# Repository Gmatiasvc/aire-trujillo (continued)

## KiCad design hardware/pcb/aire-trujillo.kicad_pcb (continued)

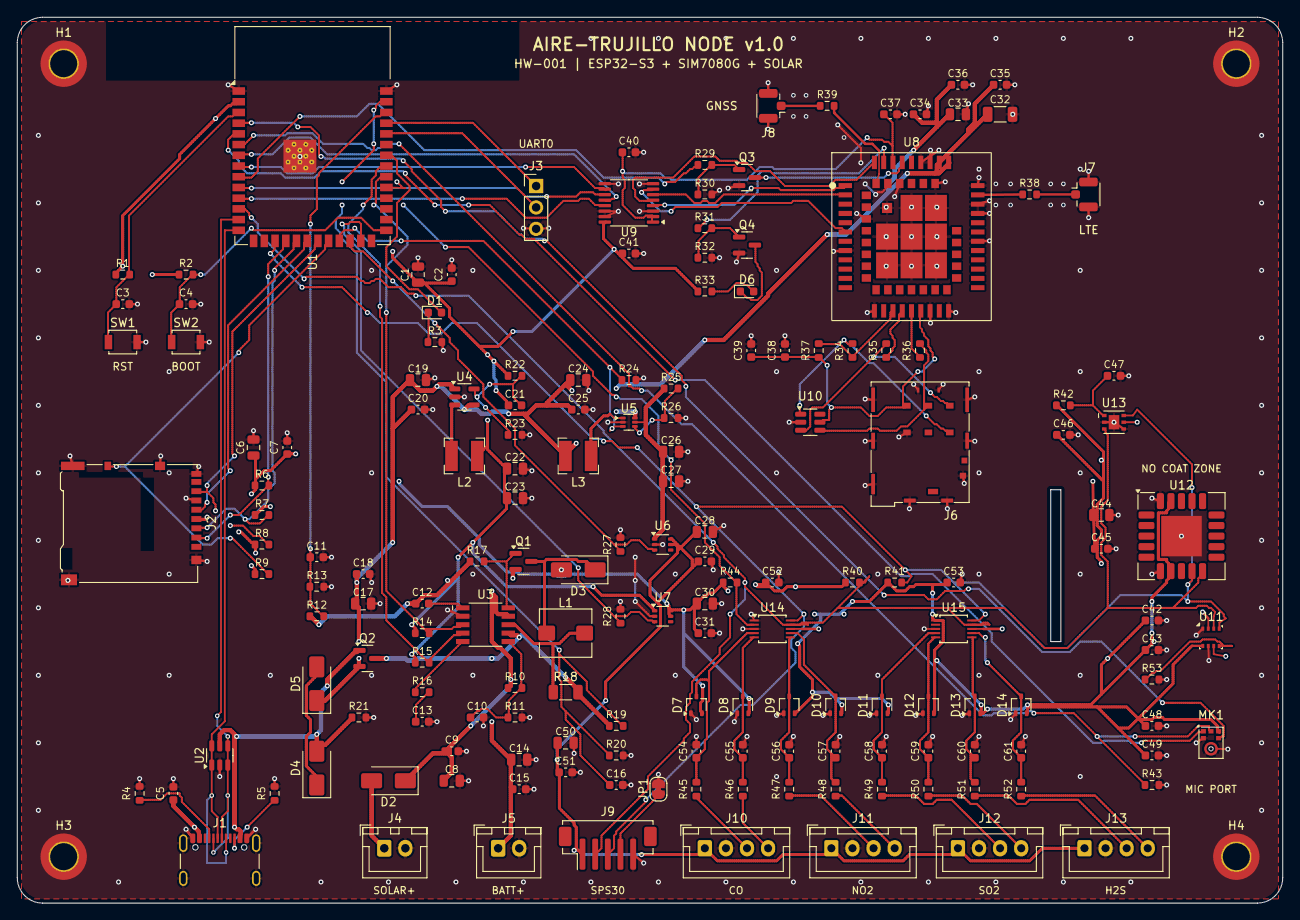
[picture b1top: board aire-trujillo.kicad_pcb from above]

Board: 4 copper layers, 150.0 x 105.0 mm, 171 parts (0 on the bottom side), 96 nets.

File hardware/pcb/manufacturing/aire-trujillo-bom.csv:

"Refs","Value","Footprint","Qty","DNP"
"C1,C6,C8,C19,C24,C28,C30,C33,C44,C50","10uF","Capacitor_SMD:C_0805_2012Metric","10",""
"C2,C4,C5,C7,C9,C11,C12,C15,C16,C18,C20,C25,C29,C31,C35,C38,C40-C43,C45,C47,C48,C51-C61","100nF","Capacitor_SMD:C_0603_1608Metric","34",""
"C3,C34,C37,C46,C49","1uF","Capacitor_SMD:C_0603_1608Metric","5",""
"C10","10nF","Capacitor_SMD:C_0603_1608Metric","1",""
"C13","220nF","Capacitor_SMD:C_0603_1608Metric","1",""
"C14,C17,C22,C23,C26,C27","22uF","Capacitor_SMD:C_0805_2012Metric","6",""
"C21","10pF","Capacitor_SMD:C_0603_1608Metric","1",""
"C32","100uF","Capacitor_SMD:C_1206_3216Metric","1",""
"C36,C39","33pF","Capacitor_SMD:C_0603_1608Metric","2",""
"D1","GREEN","LED_SMD:LED_0603_1608Metric","1",""
"D2-D5","SS34","Diode_SMD:D_SMA","4",""
"D6","BLUE_NET","LED_SMD:LED_0603_1608Metric","1",""
"D7-D14","BAT54S","Package_TO_SOT_SMD:SOT-323_SC-70","8",""
"H1-H4","M3_IP66","MountingHole:MountingHole_3.2mm_M3_ISO14580_Pad_TopBottom","4",""
"J1","USB4105-xx-A","Connector_USB:USB_C_Receptacle_GCT_USB4105-xx-A_16P_TopMnt_Horizontal","1",""
"J2","DM3AT-SF-PEJM5","Connector_Card:microSD_HC_Hirose_DM3AT-SF-PEJM5","1",""
"J3","UART0_DBG","Connector_PinHeader_2.54mm:PinHeader_1x03_P2.54mm_Vertical","1",""
"J4","SOLAR_IN","Connector_JST:JST_XH_B2B-XH-A_1x02_P2.50mm_Vertical","1",""
"J5","BATT_1S_LIION","Connector_JST:JST_XH_B2B-XH-A_1x02_P2.50mm_Vertical","1",""
"J6","SF72S006_1V8_SIM","Connector_JAE:JAE_SIM_Card_SF72S006","1",""
"J7","LTE_ANT_UFL","Connector_Coaxial:U.FL_Hirose_U.FL-R-SMT-1_Vertical","1",""
"J8","GNSS_ANT_UFL","Connector_Coaxial:U.FL_Hirose_U.FL-R-SMT-1_Vertical","1",""
"J9","SPS30_ZHR5","Connector_JST:JST_ZH_B5B-ZR-SM4-TF_1x05-1MP_P1.50mm_Vertical","1",""
"J10","ZE03_CO_XH4","Connector_JST:JST_XH_B4B-XH-A_1x04_P2.50mm_Vertical","1",""
"J11","ZE03_NO2_XH4","Connector_JST:JST_XH_B4B-XH-A_1x04_P2.50mm_Vertical","1",""
"J12","ZE03_SO2_XH4","Connector_JST:JST_XH_B4B-XH-A_1x04_P2.50mm_Vertical","1",""
"J13","ZE03_H2S_XH4","Connector_JST:JST_XH_B4B-XH-A_1x04_P2.50mm_Vertical","1",""
"JP1","I2C_SEL","Jumper:SolderJumper-2_P1.3mm_Bridged_RoundedPad1.0x1.5mm","1",""
"L1","22uH","Inductor_SMD:L_Bourns_SRP5030T","1",""
"L2","1.5uH","Inductor_SMD:L_Bourns-SRN4018","1",""
"L3","1.0uH","Inductor_SMD:L_Bourns-SRN4018","1",""
"MK1","ICS-43434","Sensor_Audio:InvenSense_ICS-43434-6_3.5x2.65mm","1",""
"Q1,Q2","AO3401A","Package_TO_SOT_SMD:SOT-23","2",""
"Q3,Q4","BSS138","Package_TO_SOT_SMD:SOT-23","2",""
"R1,R2,R6-R9,R14,R15,R17,R37,R44","10k","Resistor_SMD:R_0603_1608Metric","11",""
"R3,R29,R31,R33,R45-R52","1k","Resistor_SMD:R_0603_1608Metric","12",""
"R4,R5","5.1k","Resistor_SMD:R_0603_1608Metric","2",""
"R10,R19-R21,R23,R24,R26-R28,R30,R32,R43","100k","Resistor_SMD:R_0603_1608Metric","12",""
"R11","16.5k","Resistor_SMD:R_0603_1608Metric","1",""
"R12","470k","Resistor_SMD:R_0603_1608Metric","1",""
"R13","47k","Resistor_SMD:R_0603_1608Metric","1",""
"R16","120R","Resistor_SMD:R_0603_1608Metric","1",""
"R18","0.12R_1W","Resistor_SMD:R_1206_3216Metric","1",""
"R22","453k","Resistor_SMD:R_0603_1608Metric","1",""
"R25","732k","Resistor_SMD:R_0603_1608Metric","1",""
"R34-R36","22","Resistor_SMD:R_0603_1608Metric","3",""
"R38,R39","0R_RF","Resistor_SMD:R_0603_1608Metric","2",""
"R40,R41","4.7k","Resistor_SMD:R_0603_1608Metric","2",""
"R42","22R","Resistor_SMD:R_0603_1608Metric","1",""
"R53","0R","Resistor_SMD:R_0603_1608Metric","1",""
"SW1","RST","Button_Switch_SMD:SW_SPST_B3U-1000P","1",""
"SW2","BOOT","Button_Switch_SMD:SW_SPST_B3U-1000P","1",""
"U1","ESP32-S3-WROOM-1-N16R8","RF_Module:ESP32-S3-WROOM-1","1",""
"U2","USBLC6-2SC6","Package_TO_SOT_SMD:SOT-23-6","1",""
"U3","CN3791","aire-trujillo:cn3791","1",""
"U4","TLV62569DBV","Package_TO_SOT_SMD:SOT-23-5","1",""
"U5","TPS61023DRLR","Package_TO_SOT_SMD:SOT-563","1",""
"U6,U7","TPS22919DCKR","Package_TO_SOT_SMD:SOT-363_SC-70-6","2",""
"U8","SIM7080G","aire-trujillo:SIMCom_SIM7080G","1",""
"U9","SN74AVC4T245PW","Package_SO:TSSOP-16_4.4x5mm_P0.65mm","1",""
"U10","ESDA6V1-5SC6","Package_TO_SOT_SMD:SOT-23-6","1",""
"U11","BME280","Package_LGA:Bosch_LGA-8_2.5x2.5mm_P0.65mm_ClockwisePinNumbering","1",""
"U12","SCD41-D-R2","Sensor:Sensirion_SCD4x-1EP_10.1x10.1mm_P1.25mm_EP4.8x4.8mm","1",""
"U13","SGP40","aire-trujillo:sgp40","1",""
"U14","ADS1115_CO_NO2","Package_SO:TSSOP-10_3x3mm_P0.5mm","1",""
"U15","ADS1115_SO2_H2S","Package_SO:TSSOP-10_3x3mm_P0.5mm","1",""

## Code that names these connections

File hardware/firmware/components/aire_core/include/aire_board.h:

#ifndef AIRE_BOARD_H
#define AIRE_BOARD_H

/*
 * aire-trujillo — Mapa Definitivo de Pines, Buses y Reglas de Hardware (HW-001 v1.0)
 * MCU: ESP32-S3-WROOM-1-N16R8 (16 MB QIO Flash / 8 MB Octal PSRAM)
 * Sincronizado exactamente con hardware/doc/specs.md y aire-trujillo.kicad_pcb.
 */

/* Bus I2S — InvenSense ICS-43434 (MK1, Canal Izquierdo LR=GND) */
#define AIRE_GPIO_I2S_SCK       4
#define AIRE_GPIO_I2S_WS        5
#define AIRE_GPIO_I2S_SD        6

/* Módem Celular / GNSS — SIMCom SIM7080G (U8) vía SN74AVC4T245 (U9) y BSS138 (Q3) */
#define AIRE_GPIO_MODEM_STATUS  7
#define AIRE_GPIO_MODEM_DTR     15
#define AIRE_GPIO_MODEM_PWRKEY  16
#define AIRE_GPIO_MODEM_TXD     17   /* ESP32 TX -> U8 RXD */
#define AIRE_GPIO_MODEM_RXD     18   /* ESP32 RX <- U8 TXD */

/* Bus I2C Principal (3.3 V conmutado 3V3_SENS, R40/R41 4.7k pull-ups) */
#define AIRE_GPIO_I2C_SDA       8
#define AIRE_GPIO_I2C_SCL       9
#define AIRE_I2C_FREQ_HZ        100000U

/* Direcciones I2C de 7 bits verificadas en esquemático */
#define AIRE_I2C_ADDR_ADS1115_1 0x48U  /* U14: ADDR=GND -> CO (AIN0/1), NO2 (AIN2/3) */
#define AIRE_I2C_ADDR_ADS1115_2 0x49U  /* U15: ADDR=3V3_SENS -> SO2 (AIN0/1), H2S (AIN2/3) */
#define AIRE_I2C_ADDR_SGP40     0x59U  /* U13: VOC index */
#define AIRE_I2C_ADDR_SCD41     0x62U  /* U12: CO2 NDIR */
#define AIRE_I2C_ADDR_SPS30     0x69U  /* J9 : SPS_SEL=GND (JP1) */
#define AIRE_I2C_ADDR_BME280    0x76U  /* U11: BME_SDO=GND (R53 0R) */

/* Bus SPI — Socket MicroSD Hirose DM3AT-SF-PEJM5 (J2) */
#define AIRE_GPIO_SD_CS         10
#define AIRE_GPIO_SD_MOSI       11
#define AIRE_GPIO_SD_CLK        12
#define AIRE_GPIO_SD_MISO       13
#define AIRE_GPIO_SD_CD         14

/* Control de Potencia y Load Switches (TPS61023 U5 + 2x TPS22919 U6/U7) */
#define AIRE_GPIO_PWR_5V_EN     21   /* Habilita Boost 5V_BOOST (U5 TPS61023) */
#define AIRE_GPIO_EN_SENS_5V    47   /* Habilita 5V_SENS (U6 para SPS30 + 4x ZE03) */
#define AIRE_GPIO_EN_SENS_3V3   48   /* Habilita 3V3_SENS (U7 para I2C, ADCs, MK1, SD) */

/* Interrupción ADC y Telemetría de Carga MPPT CN3791 (U3) / LED */
#define AIRE_GPIO_ADS_ALERT     38   /* U14 ALERT/RDY open-drain (R44 10k pull-up) */
#define AIRE_GPIO_CHG_STAT      39   /* U3 CHG_STAT open-drain (R14 10k pull-up) */
#define AIRE_GPIO_CHG_DONE      40   /* U3 CHG_DONE open-drain (R15 10k pull-up) */
#define AIRE_GPIO_LED_SYS       41   /* LED verde D1 vía R3 1k */

/* Consola Serie Debug UART0 (J3) */
#define AIRE_GPIO_UART0_RXD     44
#define AIRE_GPIO_UART0_TXD     43

/* Telemetría Analógica de Energía (ADC1 ESP32-S3) */
#define AIRE_GPIO_VBAT_ADC      1    /* ADC1_CH0: R19 100k / R20 100k (x2.0) */
#define AIRE_GPIO_VSOLAR_ADC    2    /* ADC1_CH1: R12 470k / R13 47k  (x11.0) */
#define AIRE_VBAT_DIV_NUM       2.0f
#define AIRE_VSOLAR_DIV_NUM     11.0f

/* Temporizaciones Hardware Seguras (ms) */
#define AIRE_SETTLE_3V3_SENS_MS 10U
#define AIRE_SETTLE_5V_BOOST_MS 5U
#define AIRE_SETTLE_5V_SENS_MS  20U
#define AIRE_MODEM_PWRKEY_MS    1250U

#endif /* AIRE_BOARD_H */
